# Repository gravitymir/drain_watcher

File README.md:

# drain_watcher

Логгер тока утечки автомобильного аккумулятора: шунт в минусе аккумулятора,
плата-датчик на INA228 снимает с него напряжение и отдаёт замеры по I2C внешнему
контроллеру (ESP32 и т.п.). Контроллер питается от пауэрбанка, поднимает точку доступа
Wi-Fi и отдаёт веб-страницу с историей.

- [`hardware/`](hardware/) — плата KiCad 10 (схема, разводка, гербера, BOM/CPL для JLCPCB)
  и скрипты, которые её собирают. Подробности — в [hardware/README.md](hardware/README.md).
- [`firmware/ina228/`](firmware/ina228) — драйвер датчика на Rust, `no_std`, поверх
  `embedded-hal 1.0`. Без привязки к контроллеру: ему нужна только шина I2C, так что
  он одинаково встанет и в ESP-IDF, и в голый `esp-hal`.
- Прошивка контроллера (ESP32, Wi-Fi AP и веб-страница с историей) — будет здесь же.

## Драйвер INA228

Главное, ради чего он написан, — два диапазона по шунту и корректный переход между ними.
Ток утечки живёт в десятках миллиампер, и узкая шкала даёт по нему вчетверо лучшее
разрешение; подробности и цифры — в [hardware/README.md](hardware/README.md#измерение-два-диапазона-и-калибровка).

```rust
use ina228::{Ina228, Range, DEFAULT_ADDRESS};

// Шунт 2.5 мОм, верх шкалы 35 А. Стартуем на узкой шкале — машина спит.
let mut sensor = Ina228::new(i2c, DEFAULT_ADDRESS, 0.0025, 35.0);
sensor.init(Range::Narrow)?;

loop {
    // Сам уйдёт на широкую шкалу, если блок проснулся, и вернётся обратно.
    let m = sensor.measure_autoranged()?;
    log(m.current_a, m.bus_v, m.die_c);
}
```

`set_range` переписывает `SHUNT_CAL` вместе с `ADCRANGE` — поменять одно без другого
через этот API нельзя, а именно так и получается тихая ошибка в четыре раза.

Сборка и тесты:

```bash
cd firmware/ina228 && cargo test
```

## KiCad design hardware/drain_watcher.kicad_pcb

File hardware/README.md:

# drain_watcher: плата v3

Логгер тока утечки автомобильного аккумулятора: ESP32-S3 и INA228 на одной плате. Питается
от того же аккумулятора через понижающий преобразователь, Wi-Fi поднимает сама: история
замеров смотрится с телефона или ноутбука через веб-страницу, без проводов к машине.

Шунт стоит на силовых шинах в минусе аккумулятора, **основной ток по плате не идёт**: она
только снимает напряжение с шунта (четырёхпроводное подключение, Kelvin) и напряжение
аккумулятора.

| | |
|---|---|
| Размер | 52 × 45.8 мм, без крепёжных отверстий, 2 слоя, 1.6 мм, медь 1 oz |
| Контроллер | ESP32-S3-WROOM-1-N8R2 (металлический экран, до +85 °C), антенна у левого края |
| Измерение | INA228 (20 бит, смещение ±1 мкВ), I2C, адрес **0x40** (A0 = A1 = GND) |
| Звук | I2S-микрофон ICS-43434 (моно) и пищалка MLT-5020 |
| Питание | BAT+ 6…24 В (AP63205, 5 В) **или** USB-C 5 В; 3.3 В — TLV75733 |
| Проверки | DRC KiCad 10: 0 нарушений на всех уровнях, схема = плата; ERC: 0 сообщений |

## Провода J2 — к шунту и аккумулятору

Четыре отверстия 1.15 мм под провод до 0.5 мм², шаг 4.6 мм. Провода впаиваются наглухо.

| Контакт | Цепь | Куда |
|---|---|---|
| 1 `SNS+` | SNS_P | измерительный винт шунта со стороны **кузова** (отдельный тонкий провод) |
| 2 `SNS-` | SNS_N | измерительный винт шунта со стороны **аккумулятора** (отдельный тонкий провод) |
| 3 `GND` | GND | та же сторона шунта, что и SNS-, но **своим** проводом |
| 4 `BAT+` | VBAT | плюс аккумулятора через **предохранитель 1 А в самом проводе** |

SNS+ и SNS- скрутите в пару и заведите прямо на измерительные винты шунта. Положительный
ток означает разряд. BAT+ теперь и питает плату (ESP32 с Wi-Fi — в среднем ~40 мА от 12 В,
пики ~150 мА), и даёт INA228 напряжение аккумулятора.

## Выводы ESP32

| Сигнал | GPIO | Вывод модуля |
|---|---|---|
| I2C SDA (INA228) | IO13 | 21 |
| I2C SCL (INA228) | IO12 | 20 |
| ALERT INA228 | IO21 | 23 — подтяжки на плате нет, включите внутреннюю |
| RGB-светодиод D8 (DIN), протокол WS2812B | IO48 | 25 — как на DevKitC-1 |
| Кнопка BOOT | IO0 | 27 |
| USB D-/D+ | IO19/IO20 | 13/14 — встроенный USB Serial/JTAG: прошивка и логи |
| Микрофон I2S SD | IO47 | 24 — данные, подтяжка 100 кОм на землю (R12) на плате |
| Микрофон I2S WS | IO14 | 22 |
| Микрофон I2S SCK | IO11 | 19 |
| Пищалка (ШИМ на затвор Q1) | IO8 | 12 |

Подтяжки I2C 4.7 кОм к 3.3 В стоят на плате.

### Пищалка

**BZ1 — MLT-5020** (LCSC C94598): электромагнитная, пассивная, 5 × 5 мм, громче всего
на резонансе 4 кГц. Стоит между модулем и кнопками. Питается от 3.3 В через ключ:
- **Q1 AO3400A** (N-MOSFET) — коммутирует минус пищалки, затвор — с IO8;
- **D7 1N4148WS** — гасит выброс катушки;
- **R11 10 кОм** — держит затвор на земле, пока ESP32 загружается (иначе при включении — писк).

Пищалка пассивная: тон задаёт прошивка частотой ШИМ на IO8 (LEDC), громкость — скважностью
(50 % — громче всего). Так можно, например, пищать тем чаще, чем больше ток утечки.

### Микрофон

**MK1 — ICS-43434** (I2S MEMS, как в Voice-Unit) в середине верхней части, над INA228.
Развязка C1 100 нФ вплотную к выводу VDD. R12 100 кОм держит линию SD на земле, пока
микрофон её отпускает (так требует даташит).
Вывод L/R на земле — левый канал, моно. Звуковой порт у него снизу: под корпусом в плате
отверстие 0.5 мм, звук заходит с **обратной стороны** — в корпусе напротив него нужно
отверстие. В прошивке: I2S, 24 бита в 32-битном слове, левый канал, частота до 48 кГц.

### Разъёмы над модулем: четыре группы

Под каждую группу — свой разъём JST PH 2.0 мм, боковой: J3–J5 — S4B-PH-K-S (C157926),
J6 — S5B-PH-K-S (C157923). Корпуса торцом к верхнему краю, кабель уходит параллельно
плате. Разъёмы впаивает завод: номера LCSC в BOM есть, заказывать **Standard PCBA**
(на Economic выводные детали не ставят). Ответная часть — корпус PHR-4 / PHR-5 с
контактами SPH-002T-P0.5L или готовый шлейф «JST PH 2.0». Названия групп — на лице под
разъёмами и на обороте у края; подписи выводов — на обороте над выводами. Группы UART и I2C — с питанием в той же четвёрке, как у типовых модулей
датчиков: модуль подключается проводами один в один.

| Группа | Выводы | GPIO ESP32-S3 |
|---|---|---|
| J3 `UART0` | GND, 3V3, TX, RX | TXD0 (GPIO43), RXD0 (GPIO44) — штатный UART0: при включении загрузчик печатает в него служебные строки |
| J4 `UART1` | GND, 3V3, TX, RX | IO42 → TX, IO41 → RX (UART1 назначается на них в прошивке) |
| J5 `I2C` | GND, 3V3, SCL, SDA | IO40 → SCL, IO39 → SDA, подтяжки 4.7 кОм (R3, R4) на плате |
| J6 `GPIO` | IO38, IO37, IO36, IO35, 5V | свободные выводы |

Шина I2C на J5 **своя**, не общая с INA228: у некоторых датчиков (например Si7021) тот же
адрес 0x40. В прошивке это второй контроллер I2C ESP32-S3.

IO35–IO37 свободны только у модулей **без восьмибитной PSRAM** (N8, N8R2). У N16R8 они
заняты памятью, поэтому такой модуль сюда не ставить. `5V` — общая шина после диодов
«ИЛИ» (~4.6 В), `3V3` — выход стабилизатора, от каждого можно взять до ~200 мА.
IO1 и IO2 никуда не выведены.

## Питание

```
BAT+ ─ D5 (B5819W) ─┬─ D3 SMF24A, C10 10 мкФ ─ U3 AP63205 ─ L1 4.7 мкГн ─ C11,C12 2×22 мкФ ─ D6 ─┐
                    (VIN, до 32 В)                                       (+5V_B)                ├─ +5V ─ U4 TLV75733 ─ +3V3
USB VBUS ────────────────────────────────────────────────────────────────────────── D4 ────────┘
```

- **D5** — защита от переполюсовки BAT+ (Шоттки, теряется ~0.4 В).
- **D3** — TVS 24 В от выбросов на входе. Машина при замерах не заводится, выше 14.4 В
  напряжение не поднимается, запас до предела AP63205 (32 В) большой.
- **D4, D6** — диоды «ИЛИ»: плата одинаково работает от аккумулятора, от USB или от
  обоих сразу, и USB-порт компьютера не получает напряжение с преобразователя.
- **USB-C** — для прошивки и логов. Подключённый к машине, компьютер оказывается
  соединённым с кузовом через GND. Ноутбук на батарее — нормально, компьютер от сети —
  нет (или через USB-изолятор).

## Шунт

Плата рассчитана на замеры **на заглушённой машине**: двигатель не запускается, машина не
едет. Тогда весь ток — это блоки, свет и вентиляторы, максимум ~20–25 А, с запасом **35 А**.

| | |
|---|---|
| Шунт | четырёхвыводной, **30 А / 75 мВ = 2.5 мОм** (например CG FL-2C 30A 75mV, класс 0.5) |
| Шкала | широкий диапазон ±163.84 мВ — до ~65 А; узкий ±40.96 мВ — до ~16 А с шагом ~31 мкА |
| Точность на утечке | ±0.4 мА по смещению INA228, после калибровки нуля — порядка ±0.05–0.1 мА |

**Запуск двигателя через шунт на 2.5 мОм недопустим**: 150–300 А его сожгут, а сгоревший в
обрыв шунт оставит машину без основной массы. Поставьте **параллельно шунту выключатель
массы** на 100–300 А: замкнут — шунт закорочен, машина ездит как обычно; разомкнут — идёт
замер.

## Измерение: два диапазона и калибровка

У INA228 полная шкала по шунту переключается битом **`ADCRANGE`** в регистре `CONFIG`.
Те же 20 бит ложатся на вчетверо меньший диапазон, то есть шаг становится вчетверо мельче:

| `ADCRANGE` | полная шкала | шаг по напряжению | на шунте 2.5 мОм |
|---|---|---|---|
| 0 — широкий | ±163.84 мВ | 312.5 нВ | до ±65 А, шаг 125 мкА |
| 1 — узкий | ±40.96 мВ | 78.125 нВ | до ±16 А, **шаг 31 мкА** |

Ток утечки — десятки миллиампер: 30 мА на 2.5 мОм дают 75 мкВ, то есть почти тысячу
отсчётов на узкой шкале и всего две с половиной сотни на широкой. Поэтому спящая машина
меряется узким диапазоном, а широкий нужен, только когда какой-то блок проснулся и утянул
больше ~16 А.

**При смене диапазона обязательно пересчитывается `SHUNT_CAL`.** Он считается как
`13107.2e6 × CURRENT_LSB × R_шунта`, и для узкого диапазона результат **умножается на 4**.
В драйвере [`firmware/ina228`](../firmware/ina228) диапазон меняется только через
`set_range`, который сразу переписывает и `SHUNT_CAL`, а `measure_autoranged` сам уходит в
широкую шкалу при переполнении узкой и возвращается, когда ток опустится ниже 80 % узкой.

**Параметры для прошивки:** `R_SHUNT = 0.0025` Ом, верх шкалы 35 А, отсюда
`CURRENT_LSB = 35 / 2¹⁹ ≈ 66.8 мкА`. Один раз — калибровка нуля (замкнуть SNS+ и SNS− и
запомнить смещение) и коэффициента (сверка с мультиметром или токовыми клещами). Делитель
VBUS занижает напряжение примерно на 1 % — тоже калибровочный коэффициент.

## Вход измерения

- **Ток**: TVS SMF24CA (двунаправленный) на проводах, затем по 10 Ом в каждую линию и
  100 нФ между входами у INA228 (как в TI, раздел 8.1).
- **Напряжение АКБ**: 10 кОм (1206) → SMF24A на землю + 100 нФ → VBUS INA228.
- **TVS на входе 24 В, а не ±5 В.** Входы INA228 выдерживают ±40 В дифференциально и
  85 В синфазно, ток в вывод — до 5 мА. TVS на 5 В при случайном касании SNS+ к +12 В
  открылся бы и замкнул аккумулятор через провод. SMF24CA при 12 В закрыт.
- **VBUS через 10 кОм** ограничивает ток при переполюсовке до 1.2 мА (меньше 5 мА).

## Заказ

JLCPCB, три файла из этой папки:

1. **`drain_watcher_gerbers.zip`** — плата. 2 слоя, FR-4, 1.6 мм, медь 1 oz, остальное по
   умолчанию. Дорожки от 0.15 мм (у падов USB-C — 0.13 мм), зазоры 0.2 мм, отверстия от 0.3 мм, via 0.6/0.3 — всё в
   стандартных нормах для двухслойки.
2. **`BOM.csv`** — 44 SMD-детали, номера LCSC проставлены. ESP32-S3, INA228, AP63205,
   TLV75733, WS2812B, ICS-43434, MLT-5020, дроссель, USB-C, кнопки и TVS — Extended; B5819W, AO3400A, 1N4148WS и пассивка — Basic (разовая плата за
   установку каждой позиции), пассивка — Basic. **Наличие проверьте при заказе**: INA228
   сейчас в дефиците (см. ниже).
3. **`pos.csv`** — координаты для монтажа (только верхняя сторона).

В просмотрщике размещения у JLCPCB проверьте:
- **U1** (модуль) — антенна к левому краю платы, за контур;
- **U2, U3, U4** — точка/ключ первого вывода — как на шелкографии;
- **D2–D6** — полоска катода как на шелкографии;
- **D8** — метка 1-го вывода как на шелкографии.

**D8 — XINGLIGHT XL-2020RGBC-WS2812B** (C5349955) вместо WS2812B-2020 (C965555, у JLCPCB
в дефиците): та же микросхема и порядок выводов (1 DO, 2 GND, 3 DI, 4 VDD), корпус 2 × 2 мм,
пады под него — своё посадочное место `gen/fp/drain_watcher_extra.pretty`. В CPL — +180°.

**MK1 (ICS-43434)** JLCPCB помечает как сложную в монтаже (LGA со звуковым отверстием) и по
умолчанию не выбирает: галочку в BOM нужно поставить вручную. После заказа деталь
проверят и могут выставить доплату за расширенный монтаж.

Поправки для JLCPCB уже внесены в `pos.csv` (`ROT_FIX` и `POS_FIX` в `gen/export.py`):
U2, U3, U4 и микрофон MK1 — +270°, транзистор Q1 и светодиод D8 — +180°, у них корпус в библиотеке EasyEDA лежит поперёк; модуль U1 — +3.62 мм
по X, у EasyEDA начало координат модуля в центре падов; USB-C J1 — 1.57 мм по Y;
разъёмы J3–J6 — к середине ряда выводов (у KiCad начало на выводе 1), J6 ещё +180°.
Проверка — `gen/jlc_check.py`: она скачивает посадочные места JLCPCB по номерам LCSC и
сравнивает их пады с нашими (`~` у кнопок, D1 и центрального пада модуля — норма).

J2 (провода к шунту и питание) — только отверстия под пайку: в BOM и CPL его нет.

**ICS-43434** (C5656610) снят с производства, остатки на складе небольшие. Если его не
окажется — «Do not place» и запаять руками (корпус LGA 3.5 × 2.65 мм, только феном).

**INA228** у JLCPCB/LCSC, DigiKey и Mouser сейчас нет (ожидается в 2027). Вариант —
выпаять из модулей Adafruit 5832 и поставить руками (MSOP-10), а в BOM исключить U2.
По выводам совместим INA226 (16 бит, шкала ±81.92 мВ) — подходит как временная замена.

## Сборка из скриптов

Плату не рисовали мышкой: схему, размещение, ручную разводку критичных цепей и шелк
описывает `gen/build.py`, остальное разводит `kroute route` через `gen/route.py`, после чего
углы скругляются дугами. Всё это — обычный Python 3 с `pcbnew` из kroute (`../autorouter`
или `KROUTE_DIR`), KiCad не нужен.

```bash
sh gen/check.sh
```

Скрипт пересобирает схему и плату, разводит её и прогоняет DRC, сверку схемы с платой и ERC
(`kroute`, отчёты `drc.rpt`, `erc.rpt`), зазоры, связность, courtyard и шелк. Выходные файлы для заказа
(BOM, гербера, сверловка, `pos.csv`, PDF платы и схемы, архив) — тоже без KiCad, их делает
`kroute gerber/drill/pos/pdf`:

```bash
sh gen/export.sh
```

### Как устроена разводка

- **Вручную** (`build.py`, заблокирована): Kelvin-пара от проводов через RC-фильтр к
  INA228, VBUS INA228, земля адреса, BAT+ → D5, via на землю у силовой части.
- **kroute** (`route.py`): всё остальное, только углы 45°, питание 0.4–0.5 мм, USB
  0.15 мм. Если у узкого пада дорожка всё же сужена меньше 0.13 мм, `route.py` доводит её
  до 0.13 (норма JLCPCB для двухслойки — от 0.127). Разводка (`drain_watcher.routes.json`)
  лежит в репозитории вместе с ключом (`.routes.key`). Пока не менялись детали, их места и
  ручная разводка, трассировщик не запускается, медь накладывает `kroute apply`, и плата
  собирается одинаково. `--reroute` — развести заново.
- **Правило проекта** `drain_watcher.kicad_dru`: мелким земляным падам со своей
  дорожкой на via (адрес INA228, земля микрофона) хватает одной тепловой перемычки к
  заливке.
- **Дуги**: каждый излом заменяется дугой радиусом до 1 мм; если дуга подошла к
  соседу ближе зазора, она откатывается обратно в излом.
- После всего `route.py` прогоняет `kroute drc`: нарушения трассировки или несоединённое —
  ошибка.

Версии без контроллера (модуль INA228 под внешний ESP32) и прошлые варианты с ESP32
остались в истории git.

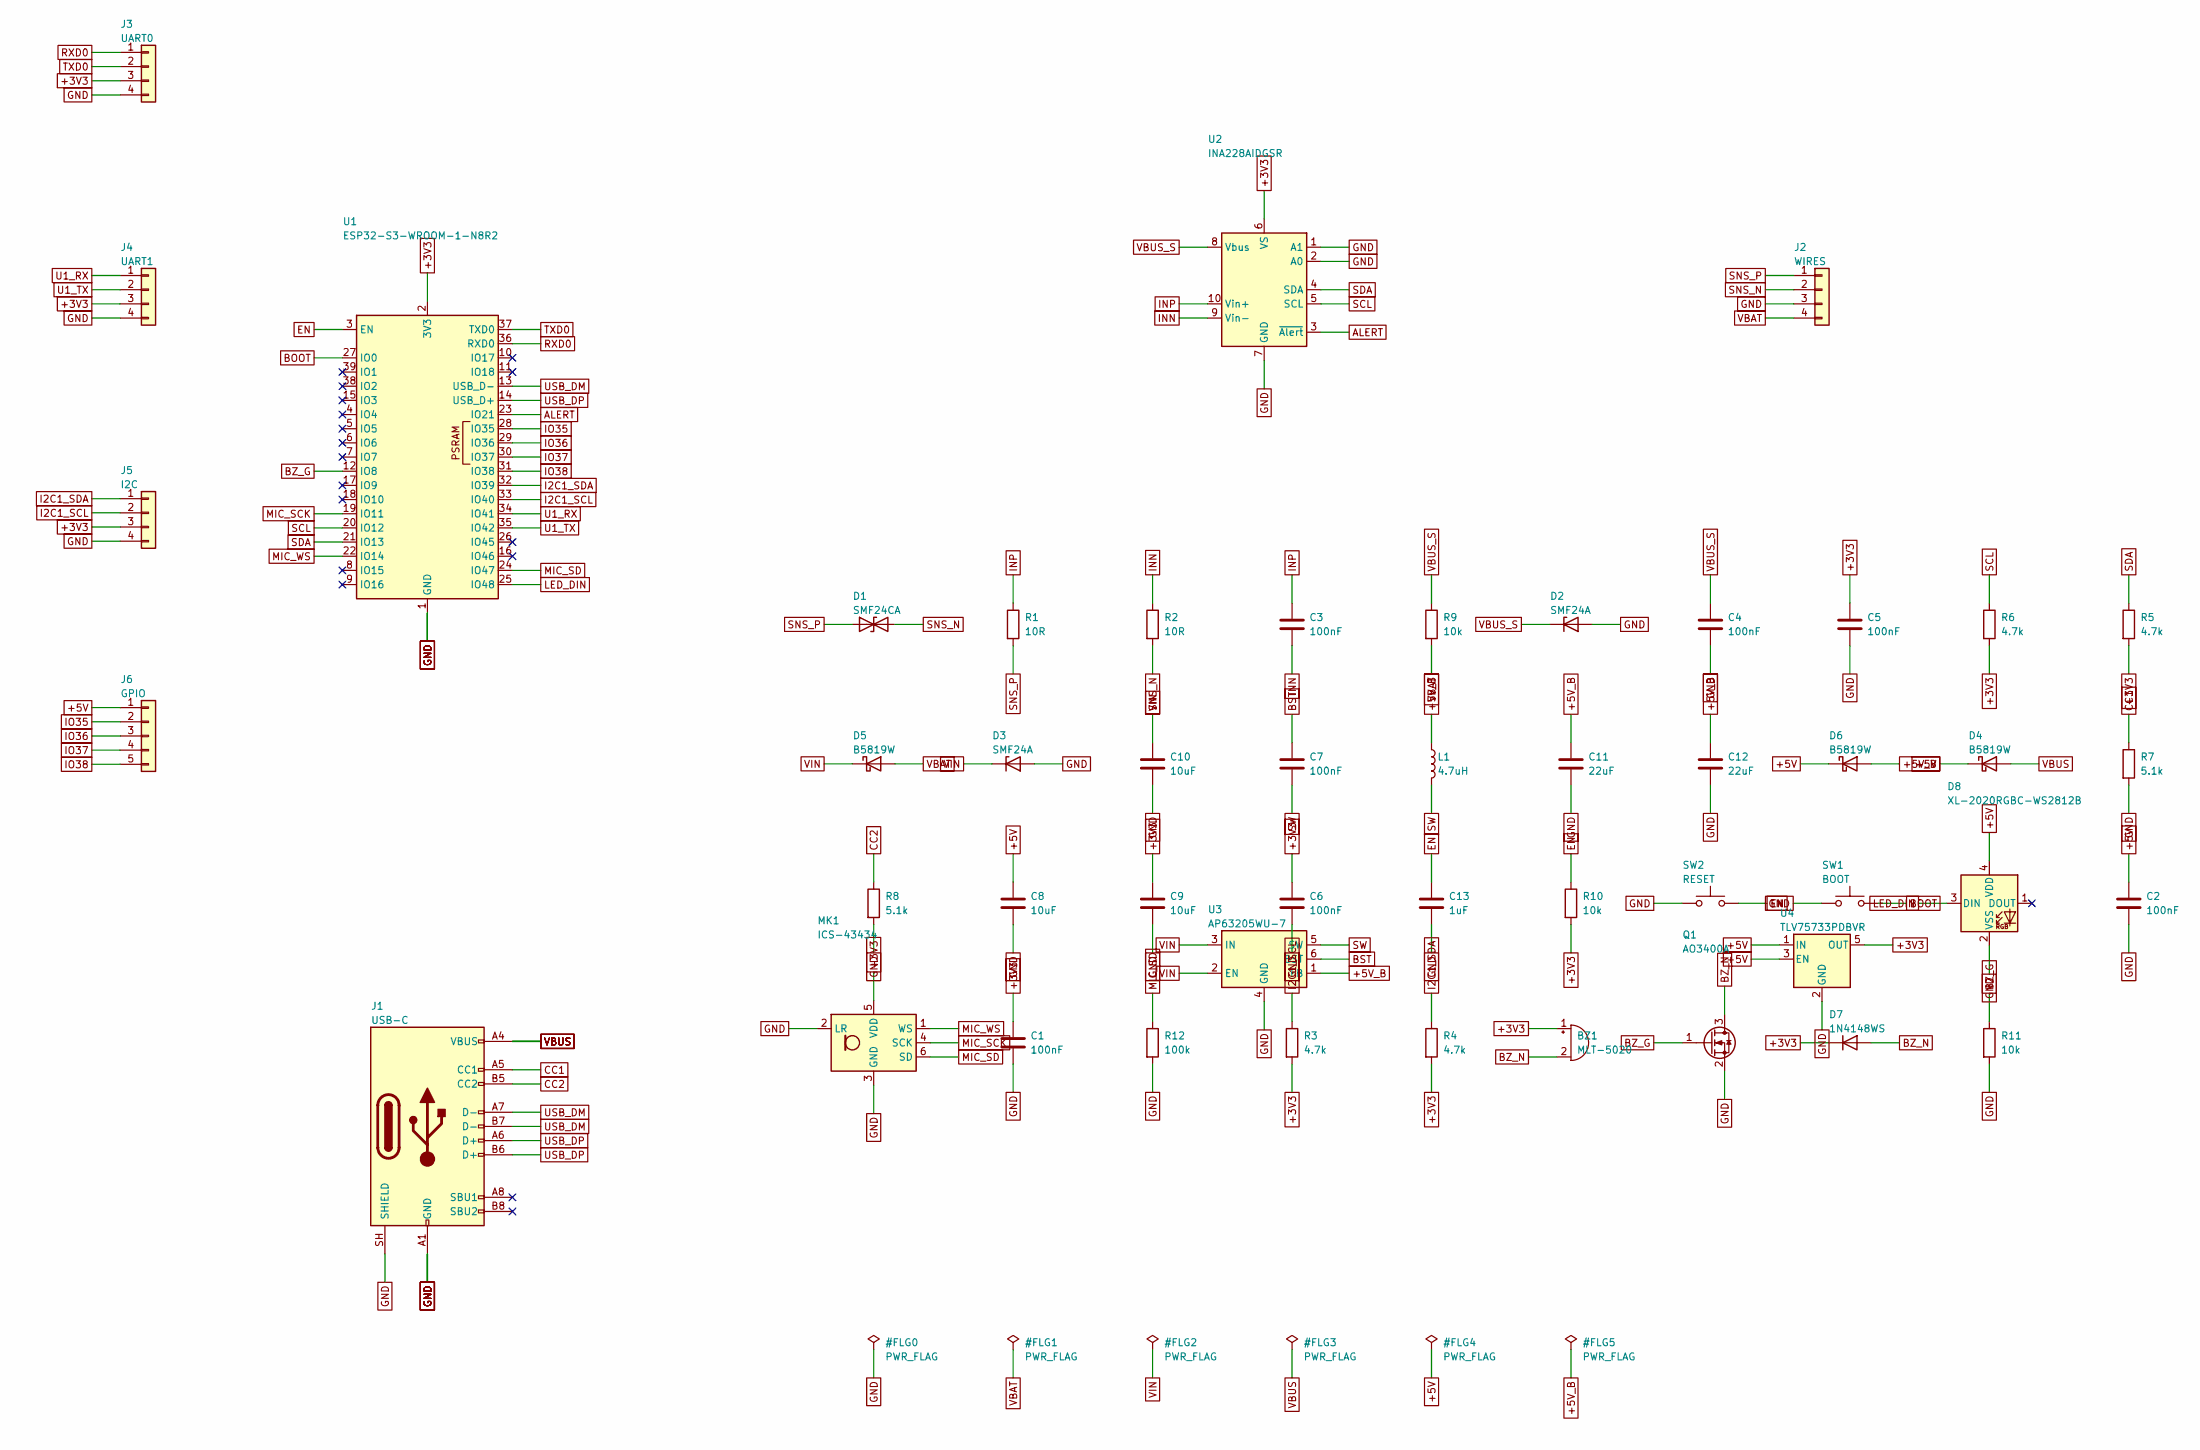
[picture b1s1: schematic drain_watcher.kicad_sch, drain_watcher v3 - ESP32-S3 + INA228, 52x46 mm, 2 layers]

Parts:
BZ1: MLT-5020; Buzzer_MLT-5020
C1, C2, C3, C4, C5, C6, C7: 100nF; C_0603_1608Metric
C8, C9, C10: 10uF; C_0805_2012Metric
C11, C12: 22uF; C_0805_2012Metric
C13: 1uF; C_0603_1608Metric
D1: SMF24CA; D_SOD-123F_Bidirectional
D2, D3: SMF24A; D_SOD-123F
D4, D5, D6: B5819W; D_SOD-123
D7: 1N4148WS; D_SOD-323
D8: XL-2020RGBC-WS2812B; LED_XL-2020RGBC
J1: USB-C; USB_C_Receptacle_HRO_TYPE-C-31-M-12
J2: WIRES; SolderWire-0.5sqmm_1x04_P4.6mm_D0.9mm_OD2.1mm
J3: UART0; JST_PH_S4B-PH-K_1x04_P2.00mm_Horizontal
J4: UART1; JST_PH_S4B-PH-K_1x04_P2.00mm_Horizontal
J5: I2C; JST_PH_S4B-PH-K_1x04_P2.00mm_Horizontal
J6: GPIO; JST_PH_S5B-PH-K_1x05_P2.00mm_Horizontal
L1: 4.7uH; L_Sunlord_SWPA4030S
MK1: ICS-43434; InvenSense_ICS-43434-6_3.5x2.65mm
Q1: AO3400A; SOT-23
R1, R2: 10R; R_0603_1608Metric
R3, R4, R5, R6: 4.7k; R_0603_1608Metric
R7, R8: 5.1k; R_0603_1608Metric
R9: 10k; R_1206_3216Metric
R10, R11: 10k; R_0603_1608Metric
R12: 100k; R_0603_1608Metric
SW1: BOOT; SW_Push_1P1T_XKB_TS-1187A
SW2: RESET; SW_Push_1P1T_XKB_TS-1187A
U1: ESP32-S3-WROOM-1-N8R2; ESP32-S3-WROOM-1
U2: INA228AIDGSR; MSOP-10_3x3mm_P0.5mm
U3: AP63205WU-7; TSOT-23-6
U4: TLV75733PDBVR; SOT-23-5

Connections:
+3V3: BZ1.1 (+), C1.1, C5.1, C6.1, C9.1, D7.1 (K), J3.3, J4.3, J5.3, MK1.5 (VDD), R3.2, R4.2, R5.2, R6.2, R10.2, U1.2 (3V3), U2.6 (VS), U4.5 (OUT)
+5V: C2.1, C8.1, D4.1 (K), D6.1 (K), D8.4 (VDD), J6.1, U4.1 (IN), U4.3 (EN)
+5V_B: C11.1, C12.1, D6.2 (A), L1.1, U3.1 (FB)
ALERT: U1.23 (IO21), U2.3 (~Alert)
BOOT: SW1.2, U1.27 (IO0)
BST: C7.1, U3.6 (BST)
BZ_G: Q1.1 (G), R11.1, U1.12 (IO8)
BZ_N: BZ1.2 (-), D7.2 (A), Q1.3 (D)
CC1: J1.A5 (CC1), R7.1
CC2: J1.B5 (CC2), R8.1
EN: C13.1, R10.1, SW2.2, U1.3 (EN)
GND: C1.2, C2.2, C4.2, C5.2, C6.2, C8.2, C9.2, C10.2, C11.2, C12.2, C13.2, D2.2 (A), D3.2 (A), D8.2 (VSS), J1.A1 (GND), J1.A12 (GND), J1.B1 (GND), J1.B12 (GND), J1.SH (SHIELD), J2.3, J3.4, J4.4, J5.4, MK1.2 (LR), MK1.3 (GND), Q1.2 (S), R7.2, R8.2, R11.2, R12.2, SW1.1, SW2.1, U1.1 (GND), U1.40 (GND), U1.41 (GND), U2.1 (A1), U2.2 (A0), U2.7 (GND), U3.4 (GND), U4.2 (GND)
I2C1_SCL: J5.2, R3.1, U1.33 (IO40)
I2C1_SDA: J5.1, R4.1, U1.32 (IO39)
INN: C3.2, R2.1, U2.9 (Vin-)
INP: C3.1, R1.1, U2.10 (Vin+)
IO35: J6.2, U1.28 (IO35)
IO36: J6.3, U1.29 (IO36)
IO37: J6.4, U1.30 (IO37)
IO38: J6.5, U1.31 (IO38)
LED_DIN: D8.3 (DIN), U1.25 (IO48)
MIC_SCK: MK1.4 (SCK), U1.19 (IO11)
MIC_SD: MK1.6 (SD), R12.1, U1.24 (IO47)
MIC_WS: MK1.1 (WS), U1.22 (IO14)
RXD0: J3.1, U1.36 (RXD0)
SCL: R6.1, U1.20 (IO12), U2.5 (SCL)
SDA: R5.1, U1.21 (IO13), U2.4 (SDA)
SNS_N: D1.2 (A2), J2.2, R2.2
SNS_P: D1.1 (A1), J2.1, R1.2
SW: C7.2, L1.2, U3.5 (SW)
TXD0: J3.2, U1.37 (TXD0)
U1_RX: J4.1, U1.34 (IO41)
U1_TX: J4.2, U1.35 (IO42)
USB_DM: J1.A7 (D-), J1.B7 (D-), U1.13 (USB_D-)
USB_DP: J1.A6 (D+), J1.B6 (D+), U1.14 (USB_D+)
VBAT: D5.2 (A), J2.4, R9.2
VBUS: D4.2 (A), J1.A4 (VBUS), J1.A9 (VBUS), J1.B4 (VBUS), J1.B9 (VBUS)
VBUS_S: C4.1, D2.1 (K), R9.1, U2.8 (Vbus)
VIN: C10.1, D3.1 (K), D5.1 (K), U3.2 (EN), U3.3 (IN)

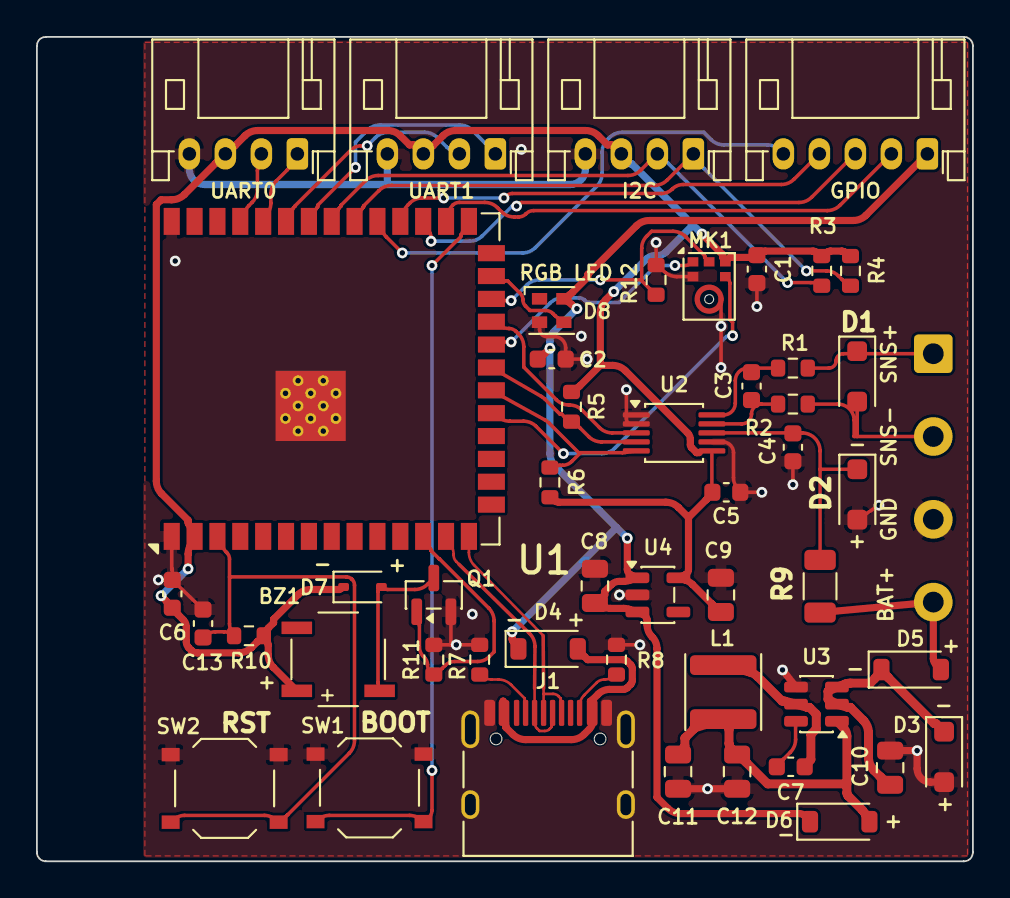
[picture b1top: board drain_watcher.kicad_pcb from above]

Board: 2 copper layers, 52.0 x 45.8 mm, 49 parts (0 on the bottom side), 39 nets.

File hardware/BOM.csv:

Comment,Designator,Footprint,LCSC Part #,Qty,Note
MLT-5020,BZ1,drain_watcher:Buzzer_MLT-5020,C94598,1,проверить наличие на складе
100nF,"C1,C2,C3,C4,C5,C6,C7",drain_watcher:C_0603_1608Metric,C14663,7,проверить наличие на складе
1uF,C13,drain_watcher:C_0603_1608Metric,C15849,1,проверить наличие на складе
10uF,"C10,C8,C9",drain_watcher:C_0805_2012Metric,C15850,3,проверить наличие на складе
22uF,"C11,C12",drain_watcher:C_0805_2012Metric,C45783,2,проверить наличие на складе
B5819W,"D4,D5,D6",drain_watcher:D_SOD-123,C8598,3,проверить наличие на складе; любой Шоттки 40 В 1 А в SOD-123 (SS14 в SMA не встанет)
SMF24A,"D2,D3",drain_watcher:D_SOD-123F,C3035828,2,проверить наличие на складе
SMF24CA,D1,drain_watcher:D_SOD-123F_Bidirectional,C3035829,1,проверить наличие на складе
1N4148WS,D7,drain_watcher:D_SOD-323,C2128,1,проверить наличие на складе
ESP32-S3-WROOM-1-N8R2,U1,drain_watcher:ESP32-S3-WROOM-1,C2913204,1,проверить наличие на складе; подойдёт ESP32-S3-WROOM-1-N8 (C2913198); N16R8 - нет: восьмибитная PSRAM занимает IO35-IO37
ICS-43434,MK1,drain_watcher:InvenSense_ICS-43434-6_3.5x2.65mm,C5656610,1,"проверить наличие на складе; снят с производства (EOL), склад мал - проверить; иначе не ставить и паять вручную"
S4B-PH-K-S,"J3,J4,J5",drain_watcher:JST_PH_S4B-PH-K_1x04_P2.00mm_Horizontal,C157926,3,проверить наличие на складе
S5B-PH-K-S,J6,drain_watcher:JST_PH_S5B-PH-K_1x05_P2.00mm_Horizontal,C157923,1,проверить наличие на складе
XL-2020RGBC-WS2812B,D8,drain_watcher:LED_XL-2020RGBC,C5349955,1,проверить наличие на складе
4.7uH,L1,drain_watcher:L_Sunlord_SWPA4030S,C57269,1,проверить наличие на складе
INA228AIDGSR,U2,drain_watcher:MSOP-10_3x3mm_P0.5mm,C2887910,1,проверить наличие на складе
10R,"R1,R2",drain_watcher:R_0603_1608Metric,C22859,2,проверить наличие на складе
4.7k,"R3,R4,R5,R6",drain_watcher:R_0603_1608Metric,C23162,4,проверить наличие на складе
5.1k,"R7,R8",drain_watcher:R_0603_1608Metric,C23186,2,проверить наличие на складе
100k,R12,drain_watcher:R_0603_1608Metric,C25803,1,проверить наличие на складе
10k,"R10,R11",drain_watcher:R_0603_1608Metric,C25804,2,проверить наличие на складе
10k,R9,drain_watcher:R_1206_3216Metric,C17902,1,проверить наличие на складе
AO3400A,Q1,drain_watcher:SOT-23,C20917,1,проверить наличие на складе
TLV75733PDBVR,U4,drain_watcher:SOT-23-5,C485517,1,проверить наличие на складе
BOOT/RESET,"SW1,SW2",drain_watcher:SW_Push_1P1T_XKB_TS-1187A,C318884,2,проверить наличие на складе
AP63205WU-7,U3,drain_watcher:TSOT-23-6,C2071056,1,проверить наличие на складе
USB-C,J1,drain_watcher:USB_C_Receptacle_HRO_TYPE-C-31-M-12,C165948,1,проверить наличие на складе
